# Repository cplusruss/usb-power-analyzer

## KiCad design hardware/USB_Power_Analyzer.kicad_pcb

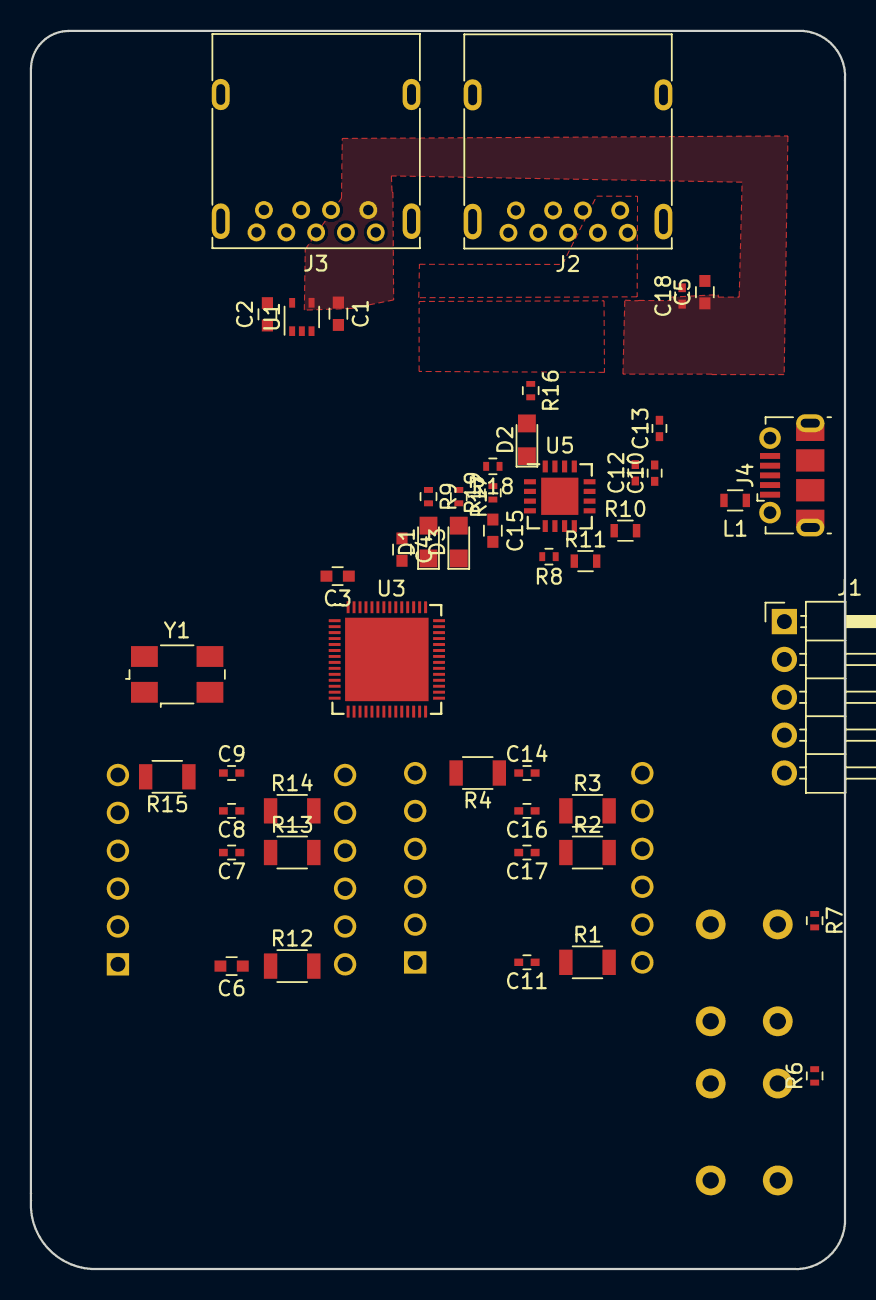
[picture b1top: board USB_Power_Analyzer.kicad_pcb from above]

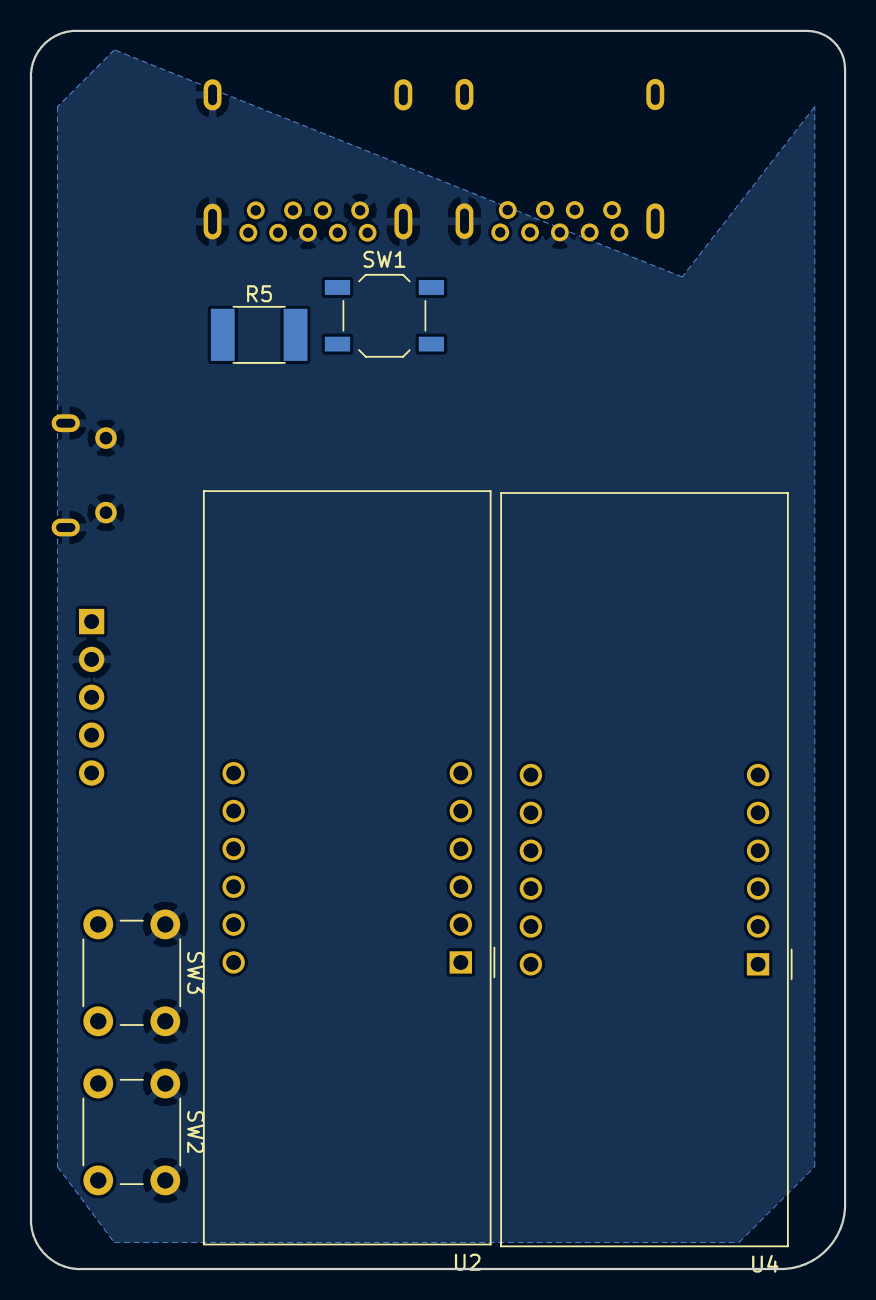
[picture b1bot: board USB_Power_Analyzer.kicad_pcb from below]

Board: 4 copper layers, 54.6 x 83.1 mm, 54 parts (6 on the bottom side), 58 nets, no tracks yet.

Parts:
C1, C2, C15: 4.7uF; C_0603
C3, C4, C5, C6: 1.0uF; C_0603
C7, C8, C9, C14, C16, C17, C18: 0.1uF; C_0402
C10, C11: 1.0uF; C_0402
C12, C13: 100nF; C_0402
D1, D2, D3: LED; LED_0805
J1: Conn_01x05_Male; Pin_Header_Angled_1x05_Pitch2.54mm
J2, J3: USB3_A; USB3_A_Molex_48393-001
J4: USB_OTG; USB_Micro-B_Molex-105017-0001
L1: Ferrite_Bead; L_0603
R1, R2, R3, R4, R12, R13, R14, R15: 40; R_1206
R5: 0.1; R_1812
R6, R7: 4.7K; R_0402
R8, R18, R19: 10K; R_0402
R9, R16, R17: 270; R_0402
R10, R11: 27; R_0603
SW1: SW_SPST; SW_SPST_TL3342
SW2, SW3: SW_Push; SW_PUSH_6mm
U1: TPS71533__SC70; SOT-353_SC-70-5
U2, U4: CC56-12CGKWA; CA56-12CGKWA
U3: CY8C4xx7LQI-4xx; QFN-56-1EP_7x7mm_Pitch0.4mm
U5: FT230XS; QFN-16-1EP_4x4mm_Pitch0.65mm
Y1: 32.768KHz; Crystal_SMD_0603-4pin_6.0x3.5mm

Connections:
+3V3: C2.1, C6.1, C7.1, C8.1, C9.1, C11.1, C14.1, C16.1, C17.1, J1.1, R1.1, R2.1, R3.1, R4.1, R6.2, R7.2, R9.1, R12.1, R13.1, R14.1, R15.1, U1.5, U3.1, U3.10, U3.14, U3.15, U3.18, U3.23, U3.36, U3.46
GND: C1.2, C2.2, C3.1, C4.1, C5.2, C6.2, C7.2, C8.2, C9.2, C10.2, C11.2, C12.2, C13.2, C14.2, C15.2, C16.2, C17.2, C18.2, J1.2, J2.4, J2.7, J2.10, J3.4, J3.7, J3.10, J4.4, J4.5, J4.6, R8.2, SW2.1, SW3.1, U1.2, U3.9, U3.11, U3.13, U3.55, U3.57, U5.5, U5.13, Y1.1, Y1.4
unnamed: C3.2, U3.56
unnamed: C4.2, U3.45
unnamed: C10.1, C12.1, U5.10, U5.11
unnamed: C13.1, C15.1, L1.2, R16.1, R17.1, R18.1, R19.1, U5.3, U5.12
unnamed: D1.1, U3.19
unnamed: D1.2, R9.2
unnamed: D2.2, R16.2
unnamed: D3.2, R17.2
unnamed: J2.1, SW1.1
unnamed: J2.2, J3.2
unnamed: J2.3, J3.3
unnamed: J2.5, J3.5
unnamed: J2.6, J3.6
unnamed: J2.8, J3.8
unnamed: J2.9, J3.9
unnamed: J4.1, L1.1
unnamed: J4.2, R11.2
unnamed: J4.3, R10.2
unnamed: R1.2, U2.12
unnamed: R2.2, U2.9
unnamed: R3.2, U2.8
unnamed: R4.2, U2.6
unnamed: R6.1, SW2.2, U3.41
unnamed: R7.1, SW3.2, U3.44
unnamed: R8.1, U5.6
unnamed: R10.1, U5.9
unnamed: R11.1, U5.8
unnamed: R12.2, U4.12
unnamed: R13.2, U4.9
unnamed: R14.2, U4.8
unnamed: R15.2, U4.6
unnamed: U2.1, U3.32
unnamed: U2.2, U3.31
unnamed: U2.3, U3.35
unnamed: U2.4, U3.30
unnamed: U2.5, U3.34
unnamed: U2.7, U3.29
unnamed: U2.10, U3.33
unnamed: U2.11, U3.28
unnamed: U3.2, Y1.3
unnamed: U3.3, Y1.2
unnamed: U3.47, U4.3
unnamed: U3.48, U4.5
unnamed: U3.49, U4.10
unnamed: U3.50, U4.1
unnamed: U3.51, U4.2
unnamed: U3.52, U4.4
unnamed: U3.53, U4.7
unnamed: U3.54, U4.11
RXD: D3.1, R19.2, U3.6, U5.4
SWDCLK: J1.4, U3.27
SWDIO: J1.5, U3.26
TXD: D2.1, R18.2, U3.5, U5.1
VBUSa: R5.2, SW1.2, U3.37
VBUSb: C1.1, C5.1, C18.1, J3.1, R5.1, U1.4, U3.38
XRESn: J1.3, U3.4

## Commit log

2018-05-20 Initial design
